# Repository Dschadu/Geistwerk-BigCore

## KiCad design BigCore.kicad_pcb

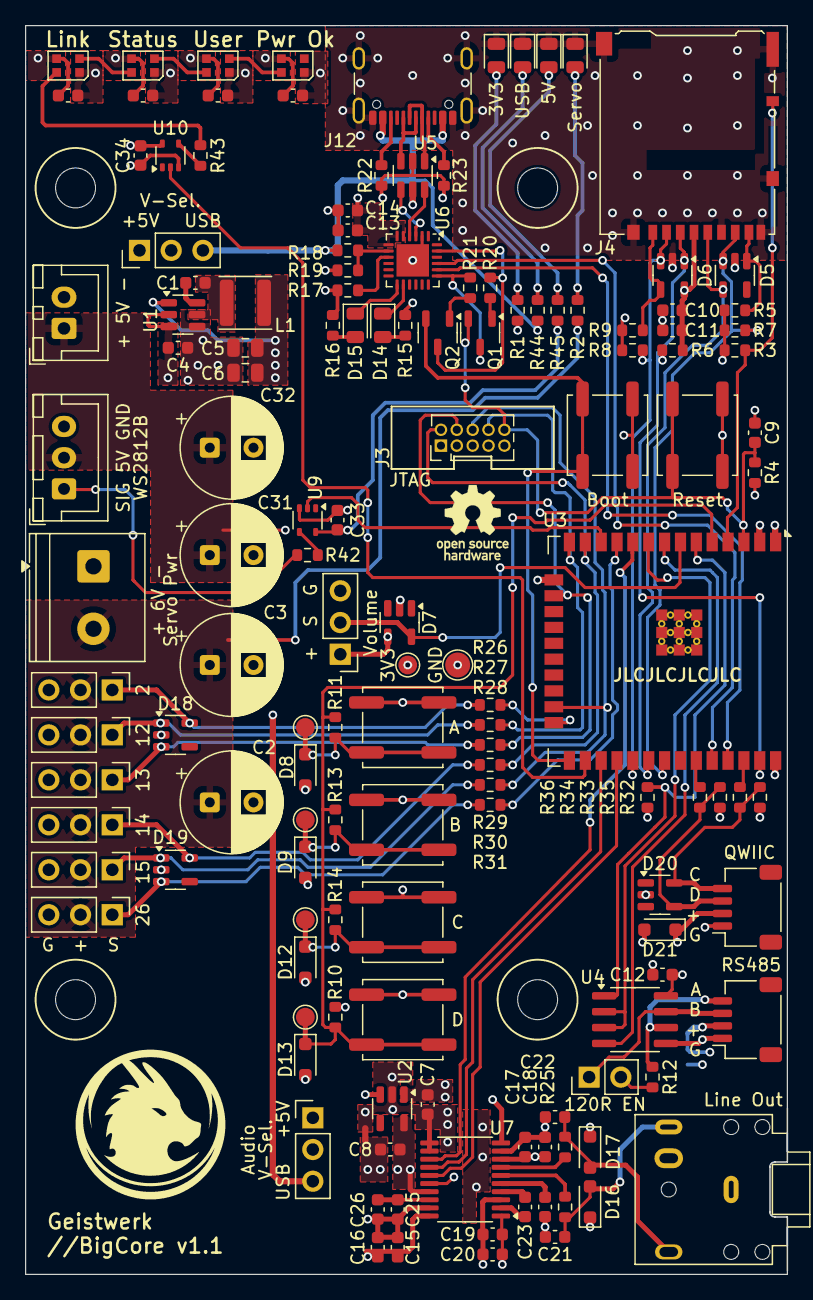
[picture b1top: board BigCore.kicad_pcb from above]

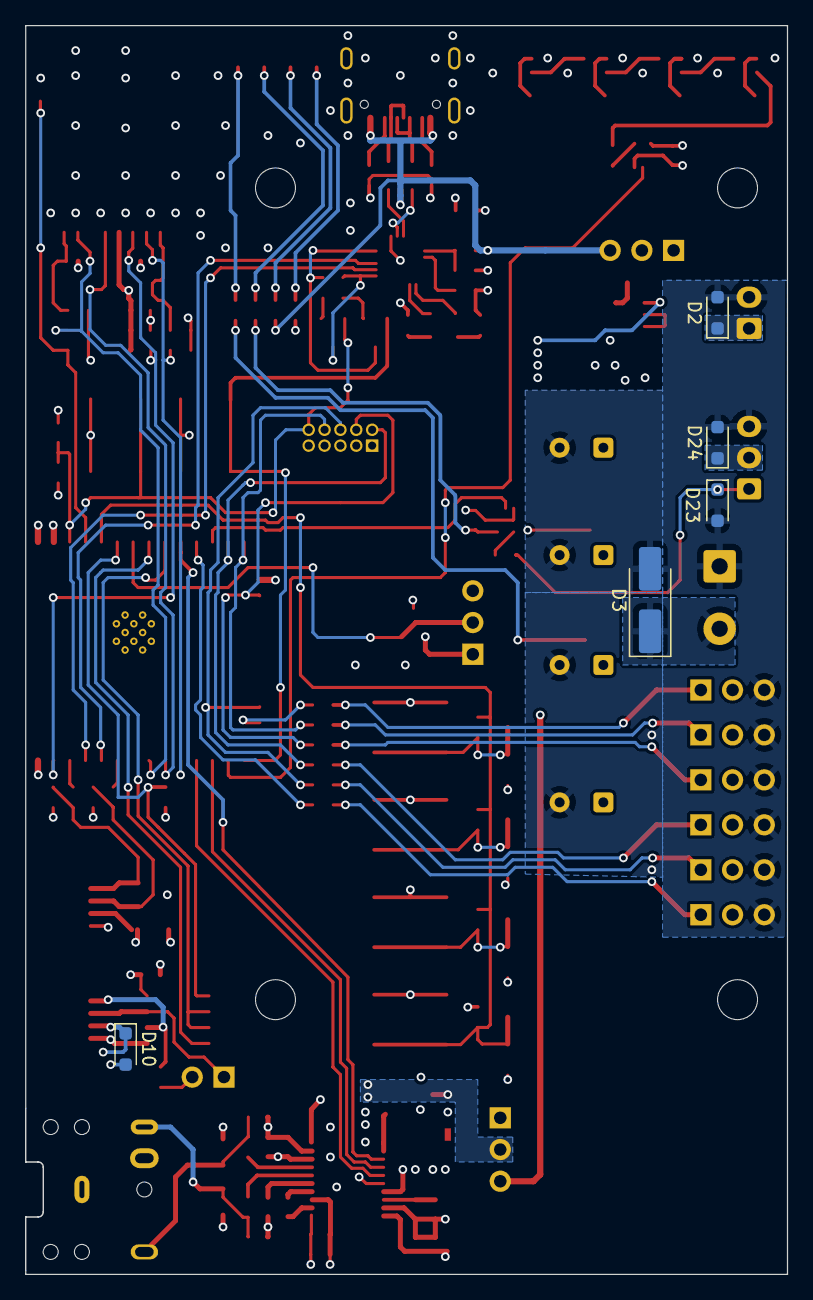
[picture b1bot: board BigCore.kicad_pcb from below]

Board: 4 copper layers, 61.0 x 100.0 mm, 151 parts (5 on the bottom side), 89 nets.

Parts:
C1, C9, C10, C12, C13, C15, C17, C19, C25, C33, C34, C35, C36, C37, C38: 100n; C_0603_1608Metric
C2, C3, C31, C32: 470µ; CP_Radial_D8.0mm_P3.50mm
C4, C11, C14, C16, C18, C20, C26: 10µ; C_0603_1608Metric
C5, C6: 22µ; C_0805_2012Metric
C7, C8: 1µ; C_0603_1608Metric
C21, C22: 2.2n; C_0603_1608Metric
C23, C24: 2.2µ; C_0603_1608Metric
D1, D4, D29, D30: Green; LED_0805_2012Metric
D2, D23, D24: TSD05DYFR; D_SOD-323_HandSoldering
D3: SMCJ13A; D_SMA_Handsoldering
D5, D6, D18, D19: ESDS314; SOT-23-5
D7, D20: ESDS312; SOT-23-5
D8, D9, D10, D12, D13, D21: ESDS311DYFR; D_SOD-323_HandSoldering
D14: TX; LED_0805_2012Metric
D15: RX; LED_0805_2012Metric
D16, D17: SD08LCC; D_SOD-323_HandSoldering
D25, D26, D27, D28: WS2812B; LED_WS2812B-2020_PLCC4_2.0x2.0mm
H1, H2, H3, H4: MountingHole; MountingHole_3.2mm_M3
H5: Logo_Open_Hardware_Small; OSHW-Logo_5.7x6mm_SilkScreen
J1: 5V In; JST_XH_B2B-XH-A_1x02_P2.50mm_Vertical
J2: Vdrive In; TerminalBlock_Phoenix_PT-1,5-2-5.0-H_1x02_P5.00mm_Horizontal
J3: JTAG; PinHeader_2x05_P1.27mm_Vertical
J4: DM3AT-SF-PEJM5; microSD_HC_Hirose_DM3AT-SF-PEJM5
J5: Volume; PinHeader_1x03_P2.54mm_Vertical
J6: Btn 0; TestPoint_Pad_D1.5mm
J7: RS485; JST_SH_SM04B-SRSS-TB_1x04-1MP_P1.00mm_Horizontal
J8: Btn 1; TestPoint_Pad_D1.5mm
J9: Btn 2; TestPoint_Pad_D1.5mm
J10: Btn 3; TestPoint_Pad_D1.5mm
J11: GND; TestPoint_Pad_D2.0mm
J12: USB_C_Receptacle_USB2.0; USB_C_Receptacle_GCT_USB4105-xx-A_16P_TopMnt_Horizontal
J13: Line Out; Jack_3.5mm_CUI_SJ1-3524N_Horizontal
J14: Servo 01; PinHeader_1x03_P2.54mm_Vertical
J15: Servo 02; PinHeader_1x03_P2.54mm_Vertical
J16: Servo 03; PinHeader_1x03_P2.54mm_Vertical
J17: Servo 04; PinHeader_1x03_P2.54mm_Vertical
J18: Servo 05; PinHeader_1x03_P2.54mm_Vertical
J19: Servo 06; PinHeader_1x03_P2.54mm_Vertical
J20: I2C; JST_SH_SM04B-SRSS-TB_1x04-1MP_P1.00mm_Horizontal
J22: WS2812; JST_XH_B3B-XH-A_1x03_P2.50mm_Vertical
JP1: RS485; PinHeader_1x02_P2.54mm_Vertical
JP2: 5V Selection Digital; PinHeader_1x03_P2.54mm_Vertical
JP3: 5V Selection Analog; PinHeader_1x03_P2.54mm_Vertical
L1: 2,2µ; L_APV_ANR4020
NT1: NetTie_2; NetTie-2_SMD_Pad0.5mm
Q1, Q2: SS8050-G; SOT-23-3
R1, R12, R15, R16, R42, R43: 120; R_0603_1608Metric
R2, R24, R25, R44, R45: 470; R_0603_1608Metric
R3, R4, R5, R6, R7, R8, R9, R20, R21, R36: 10k; R_0603_1608Metric
R10, R17: 1k; R_0603_1608Metric
R11: 4,99k; R_0603_1608Metric
R13: 1,15k; R_0603_1608Metric
R14: 300; R_0603_1608Metric
R18: 22.1k; R_0603_1608Metric
R19: 47.5k; R_0603_1608Metric
R22, R23: 5,1k; R_0603_1608Metric
R26, R27, R28, R29, R30, R31, R34, R35: 33; R_0603_1608Metric
R32, R33: 1.6k; R_0603_1608Metric
SW1: Reset; SW_Push_1P1T_NO_CK_KSC7xxJ
SW2: Boot; SW_Push_1P1T_NO_CK_KSC7xxJ
SW3: Btn 0; SW_Push_1P1T_NO_CK_KSC7xxJ
SW4: Btn 1; SW_Push_1P1T_NO_CK_KSC7xxJ
SW5: Btn 2; SW_Push_1P1T_NO_CK_KSC7xxJ
SW6: Btn 3; SW_Push_1P1T_NO_CK_KSC7xxJ
TP1: +3V3; TestPoint_Pad_D1.5mm
U1: AP63203WU; TSOT-23-6
U2: AP2112K-3.3; SOT-23-5
U3: ESP32-WROOM-32E
U4: ST3485EBDR; SOIC-8_3.9x4.9mm_P1.27mm
U5: USBLC6-2SC6; SOT-23-6
U6: CP2102N-Axx-xQFN24; QFN-24-1EP_4x4mm_P0.5mm_EP2.6x2.6mm
U7: PCM5102A; TSSOP-20_4.4x6.5mm_P0.65mm
U9, U10: 74AHCT1G17; SOT-353_SC-70-5

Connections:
+3.3V: C5.1, C6.1, C10.1, C11.1, C12.1, C13.1, C14.1, C15.1, C16.1, D6.5 (K), D7.4 (K), D10.1 (K), D21.1 (K), J3.1, J4.4 (VDD), J5.1, J7.2, J20.2, L1.2, R1.1, R3.1, R4.1, R5.1, R6.1, R7.1, R8.1, R9.1, R10.1, R15.1, R16.1, R17.1, R32.1, R33.1, R36.1, TP1.1, U1.1 (FB), U3.2 (VDD), U4.8 (VCC), U6.5 (VIO), U6.6 (VDD), U6.7 (VREGIN), U7.20 (DVDD)
+3.3VA: C8.1, C17.1, C18.1, C19.1, C20.1, U2.5 (VOUT), U7.1 (CPVDD), U7.8 (AVDD), U7.17 (XSMT)
+5V: C31.1, C32.1, C33.1, D2.1 (K), D24.1 (K), J1.1, J22.2, JP2.1 (A), JP3.1 (A), R45.1, U9.5 (VCC)
+5VD: C4.1, C34.1, C35.1, C36.1, C37.1, C38.1, D25.1 (VDD), D26.1 (VDD), D27.1 (VDD), D28.1 (VDD), JP2.2 (C), U1.2 (EN), U1.3 (IN), U10.5 (VCC)
/Controller/BOOT: Q2.2 (C), SW2.1, U3.25 (IO0)
/Controller/Buttons: D13.1 (K), J10.1, R10.2, R11.1, R13.1, R14.1, SW6.2, U3.5 (SENSOR_VN)
/Controller/EN: C9.1, J3.10, Q1.2 (C), R4.2, SW1.1, U3.3 (EN)
/Controller/I2S_BitClock: U3.10 (IO25), U7.13 (BCK)
/Controller/I2S_Data: U3.27 (IO16), U7.14 (DIN)
/Controller/I2S_LeftRightClock: U3.28 (IO17), U7.15 (LRCK)
/Controller/LED_STATUS: U3.26 (IO4), U10.2
/Controller/RS485_A: J7.4, R12.2, U4.6 (A)
/Controller/RS485_B: J7.3, JP1.1 (A), U4.7 (B)
/Controller/RS485_D: U3.8 (IO32), U4.4 (D)
/Controller/RS485_R: R36.2, U3.6 (IO34), U4.1 (R)
/Controller/RS485_~REDE: U3.9 (IO33), U4.2 (~RE), U4.3 (DE)
/Controller/RXD: U3.34 (RXD0/IO3), U6.21 (TXD)
/Controller/SCL: R35.1, U3.36 (IO22)
/Controller/SDA: R34.1, U3.33 (IO21)
/Controller/SD_CD: D6.3 (K), J4.2 (DAT3/CD), R8.2, U3.29 (IO5)
/Controller/SD_CLK: D5.4 (K), J4.5 (CLK), U3.30 (IO18)
/Controller/SD_CMD: D6.1 (K), J4.3 (CMD), R6.2, U3.37 (IO23)
/Controller/SD_DAT0: D5.3 (K), J4.7 (DAT0), R7.2, U3.31 (IO19)
/Controller/SD_Detect: J4.10 (DET_A), R3.2, U3.4 (SENSOR_VP)
/Controller/Servo_01: R26.1, U3.24 (IO2)
/Controller/Servo_02: J3.8, R27.1, U3.14 (IO12)
/Controller/Servo_03: J3.4, R28.1, U3.16 (IO13)
/Controller/Servo_04: J3.2, R29.1, U3.13 (IO14)
/Controller/Servo_05: J3.6, R30.1, U3.23 (IO15)
/Controller/Servo_06: R31.1, U3.11 (IO26)
/Controller/TXD: U3.35 (TXD0/IO1), U6.20 (RXD)
/Controller/Volume: D7.5 (K), J5.2, U3.7 (IO35)
/Controller/WS2812_Bus: U3.12 (IO27), U9.2
/Power Supply/5VA_In: C7.1, JP3.2 (C), U2.1 (VIN), U2.3 (EN)
GND: C2.2, C3.2, C4.2, C5.2, C6.2, C7.2, C9.2, C10.2, C11.2, C12.2, C13.2, C14.2, C15.2, C16.2, C25.2, C26.2, C31.2, C32.2, C33.2, C34.2, C35.2, C36.2, C37.2, C38.2, D1.1 (K), D2.2 (A), D3.2 (A), D4.1 (K), D5.2 (A), D6.2 (A), D7.2 (A), D8.2 (A), D9.2 (A), D10.2 (A), D12.2 (A), D13.2 (A), D18.2 (A), D19.2 (A), D20.2 (A), D21.2 (A), D23.2 (A), D24.2 (A), D25.3 (VSS), D26.3 (VSS), D27.3 (VSS), D28.3 (VSS), D29.1 (K), D30.1 (K), J1.2, J2.1, J3.3, J3.5, J3.7, J3.9, J4.6 (VSS), J4.9 (DET_B), J4.11 (SHIELD), J5.3, J7.1, J11.1, J12.A1 (GND), J12.A12 (GND), J12.B1 (GND), J12.B12 (GND), J12.S1 (SHIELD), J14.3, J15.3, J16.3, J17.3, J18.3, J19.3, J20.1, J22.3, NT1.1, R19.2, R22.1, R23.1, SW1.2, SW2.2, SW3.1, SW4.1, SW5.1, SW6.1, U1.4 (GND), U2.2 (GND), U3.1 (GND), U3.15 (GND), U3.38 (GND), U3.39 (GND), U4.5 (GND), U5.2 (GND), U6.2 (GND), U6.25 (GND), U7.10 (DEMP), U7.11 (FLT), U7.12 (SCK), U7.16 (FMT), U7.19 (DGND), U9.3 (GND), U10.3 (GND)
GNDA: C8.2, C17.2, C18.2, C19.2, C20.2, C21.2, C22.2, C24.2, D16.1 (A1), D17.1 (A1), J13.S, NT1.2, U7.3 (CPGND), U7.9 (AGND)
unnamed: D1.2 (A), R2.2
unnamed: D4.2 (A), R1.2
unnamed: D8.1 (K), J6.1, R11.2, SW3.2
unnamed: D9.1 (K), J8.1, R13.2, SW4.2
unnamed: D12.1 (K), J9.1, R14.2, SW5.2
unnamed: D14.2 (A), R15.2
unnamed: D14.1 (K), U6.14 (~TXT/GPIO.0)
unnamed: D15.2 (A), R16.2
unnamed: D15.1 (K), U6.13 (~RXT/GPIO.1)
unnamed: C21.1, D16.2 (A2), J13.T, R24.2
unnamed: C22.1, D17.2 (A2), J13.R, R25.2
unnamed: D23.1 (K), J22.1, R42.2
unnamed: D25.4 (DIN), R43.2
unnamed: D25.2 (DOUT), D26.4 (DIN)
unnamed: D26.2 (DOUT), D27.4 (DIN)
unnamed: D27.2 (DOUT), D28.4 (DIN)
unnamed: D29.2 (A), R44.2
unnamed: D30.2 (A), R45.2
unnamed: D5.1 (K), J4.8 (DAT1), R5.2
unnamed: D6.4 (K), J4.1 (DAT2), R9.2
unnamed: J12.A5 (CC1), R23.2
unnamed: J12.B5 (CC2), R22.2
unnamed: J12.A6 (D+), J12.B6 (D+), U5.3 (I/O2)
unnamed: J12.A7 (D-), J12.B7 (D-), U5.1 (I/O1)
unnamed: D18.5 (K), J14.1, R26.2
unnamed: D18.1 (K), J15.1, R27.2
unnamed: D18.3 (K), J16.1, R28.2
unnamed: D19.5 (K), J17.1, R29.2
unnamed: D19.1 (K), J18.1, R30.2
unnamed: D19.3 (K), J19.1, R31.2
unnamed: D20.4 (K), J20.3, R33.2, R34.2
unnamed: D20.5 (K), J20.4, R32.2, R35.2
unnamed: JP1.2 (B), R12.1
unnamed: Q1.1 (B), R20.2
unnamed: Q1.3 (E), R21.1, U6.19 (~RTS)
unnamed: Q2.1 (B), R21.2
unnamed: Q2.3 (E), R20.1, U6.23 (~DTR)
unnamed: R42.1, U9.4
unnamed: R43.1, U10.4
unnamed: C1.2, U1.6 (BST)
unnamed: C1.1, L1.1, U1.5 (SW)
unnamed: U5.4 (I/O2), U6.3 (D+)
unnamed: U5.6 (I/O1), U6.4 (D-)
unnamed: R18.2, R19.1, U6.8 (VBUS)
unnamed: R17.2, U6.9 (~RST)
unnamed: C23.2, U7.4 (CAPM)
unnamed: C23.1, U7.2 (CAPP)
unnamed: C25.1, C26.1, U7.18 (LDOO)
unnamed: R24.1, U7.6 (OUTL)
unnamed: R25.1, U7.7 (OUTR)
unnamed: C24.1, U7.5 (VNEG)
VBUS: J12.A4 (VBUS), J12.A9 (VBUS), J12.B4 (VBUS), J12.B9 (VBUS), JP2.3 (B), JP3.3 (B), R18.1, R44.1, U5.5 (VBUS)
Vdrive: C2.1, C3.1, D3.1 (K), J2.2, J14.2, J15.2, J16.2, J17.2, J18.2, J19.2, R2.1

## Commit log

2026-05-09 Changed some labes, fixed RS485 Line Fixed Servo-Pin Header and Audio-Pin Header label. Added 10k Pullup to RS485 R-Line
2026-06-26 Updated Docs
    Updated PCB image
    Updated schematic
    Updated BOM
